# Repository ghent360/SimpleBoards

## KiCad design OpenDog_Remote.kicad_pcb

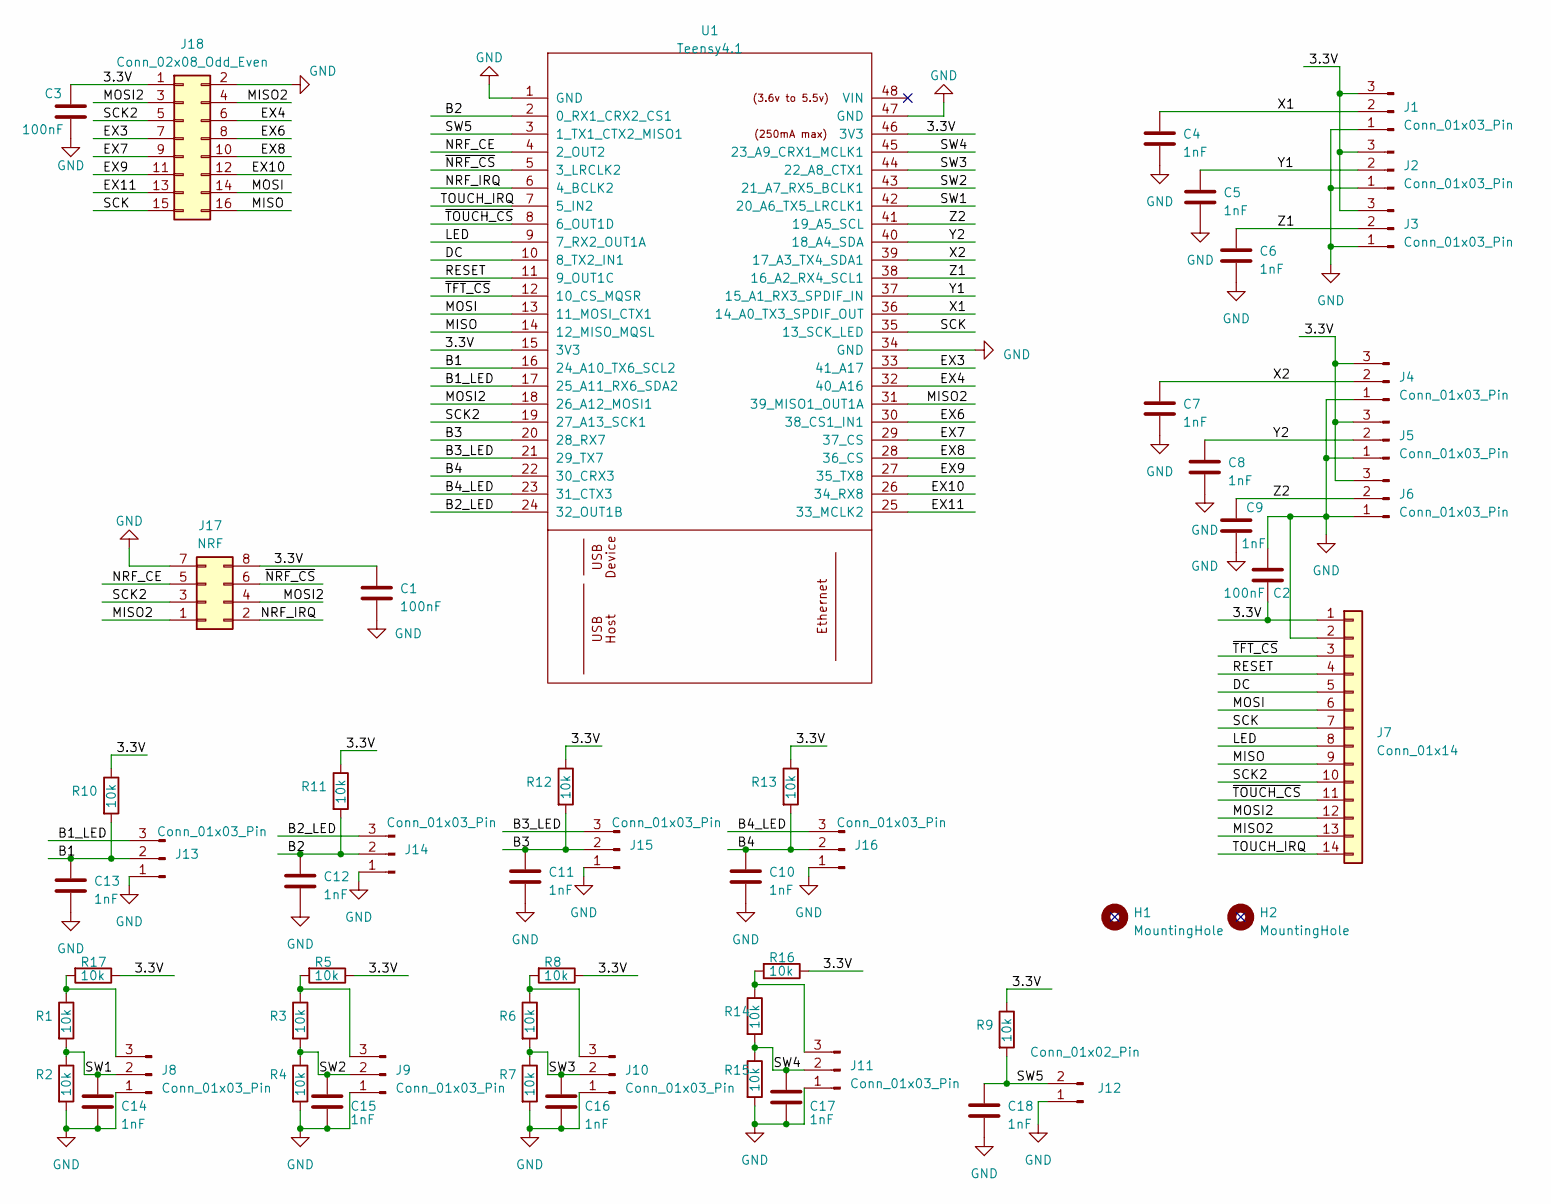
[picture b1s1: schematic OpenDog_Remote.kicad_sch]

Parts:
C1, C2, C3: 100nF; C_0603_1608Metric; JLC Part # C14663
C4, C5, C6, C7, C8, C9, C10, C11, C12, C13, C14, C15, C16, C17, C18: 1nF; C_0402_1005Metric; JLC Part # C1523
H1, H2: MountingHole; MountingHole_3.2mm_M3
J1, J2, J3, J4, J5, J6, J8, J9, J10, J11, J13, J14, J15, J16: Conn_01x03_Pin; JST_XH_B3B-XH-A_1x03_P2.50mm_Vertical; JLC Part # C722693
J7: Conn_01x14; PinHeader_1x14_P2.54mm_Vertical; JLC Part # C2905490
J12: Conn_01x02_Pin; JST_XH_B2B-XH-A_1x02_P2.50mm_Vertical; JLC Part # C2979476
J17: NRF; PinSocket_2x04_P2.54mm_Vertical; JLC Part # C2834799
J18: Conn_02x08_Odd_Even; PinSocket_2x08_P2.54mm_Vertical; JLC Part # C92267
R1, R2, R3, R4, R5, R6, R7, R8, R9, R10, R11, R12, R13, R14, R15, R16, R17: 10k; R_0402_1005Metric; JLC Part # C25744
U1: Teensy4.1; Teensy41-Simple

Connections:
/3.3V: C1.1, C2.2, C3.1, J1.3, J2.3, J3.3, J4.3, J5.3, J6.3, J7.1, J17.8, J18.1, R5.1, R8.1, R9.1, R10.1, R11.1, R12.1, R13.1, R16.1, R17.1, U1.15 (3V3), U1.46 (3V3)
/B1: C13.1, J13.2, R10.2, U1.16 (24_A10_TX6_SCL2)
/B1_LED: J13.3, U1.17 (25_A11_RX6_SDA2)
/B2: C12.1, J14.2, R11.2, U1.2 (0_RX1_CRX2_CS1)
/B2_LED: J14.3, U1.24 (32_OUT1B)
/B3: C11.1, J15.2, R12.2, U1.20 (28_RX7)
/B3_LED: J15.3, U1.21 (29_TX7)
/B4: C10.1, J16.2, R13.2, U1.22 (30_CRX3)
/B4_LED: J16.3, U1.23 (31_CTX3)
/DC: J7.5, U1.10 (8_TX2_IN1)
/EX3: J18.7, U1.33 (41_A17)
/EX4: J18.6, U1.32 (40_A16)
/EX6: J18.8, U1.30 (38_CS1_IN1)
/EX7: J18.9, U1.29 (37_CS)
/EX8: J18.10, U1.28 (36_CS)
/EX9: J18.11, U1.27 (35_TX8)
/EX10: J18.12, U1.26 (34_RX8)
/EX11: J18.13, U1.25 (33_MCLK2)
/LED: J7.8, U1.9 (7_RX2_OUT1A)
/MISO: J7.9, J18.16, U1.14 (12_MISO_MQSL)
/MISO2: J7.13, J17.1, J18.4, U1.31 (39_MISO1_OUT1A)
/MOSI: J7.6, J18.14, U1.13 (11_MOSI_CTX1)
/MOSI2: J7.12, J17.4, J18.3, U1.18 (26_A12_MOSI1)
/NRF_CE: J17.5, U1.4 (2_OUT2)
/NRF_IRQ: J17.2, U1.6 (4_BCLK2)
/RESET: J7.4, U1.11 (9_OUT1C)
/SCK: J7.7, J18.15, U1.35 (13_SCK_LED)
/SCK2: J7.10, J17.3, J18.5, U1.19 (27_A13_SCK1)
/SW1: C14.1, J8.2, R1.2, R2.1, U1.42 (20_A6_TX5_LRCLK1)
/SW2: C15.1, J9.2, R3.2, R4.1, U1.43 (21_A7_RX5_BCLK1)
/SW3: C16.1, J10.2, R6.2, R7.1, U1.44 (22_A8_CTX1)
/SW4: C17.1, J11.2, R14.2, R15.1, U1.45 (23_A9_CRX1_MCLK1)
/SW5: C18.1, J12.2, R9.2, U1.3 (1_TX1_CTX2_MISO1)
/TOUCH_IRQ: J7.14, U1.7 (5_IN2)
/X1: C4.1, J1.2, U1.36 (14_A0_TX3_SPDIF_OUT)
/X2: C7.1, J4.2, U1.39 (17_A3_TX4_SDA1)
/Y1: C5.1, J2.2, U1.37 (15_A1_RX3_SPDIF_IN)
/Y2: C8.1, J5.2, U1.40 (18_A4_SDA)
/Z1: C6.1, J3.2, U1.38 (16_A2_RX4_SCL1)
/Z2: C9.1, J6.2, U1.41 (19_A5_SCL)
/~NRF_CS: J17.6, U1.5 (3_LRCLK2)
/~TFT_CS: J7.3, U1.12 (10_CS_MQSR)
/~TOUCH_CS: J7.11, U1.8 (6_OUT1D)
GND: C1.2, C2.1, C3.2, C4.2, C5.2, C6.2, C7.2, C8.2, C9.2, C10.2, C11.2, C12.2, C13.2, C14.2, C15.2, C16.2, C17.2, C18.2, J1.1, J2.1, J3.1, J4.1, J5.1, J6.1, J7.2, J8.1, J9.1, J10.1, J11.1, J12.1, J13.1, J14.1, J15.1, J16.1, J17.7, J18.2, R2.2, R4.2, R7.2, R15.2, U1.1 (GND), U1.34 (GND), U1.47 (GND)
unnamed: J8.3, R1.1, R17.2
unnamed: J9.3, R3.1, R5.2
unnamed: J10.3, R6.1, R8.2
unnamed: J11.3, R14.1, R16.2

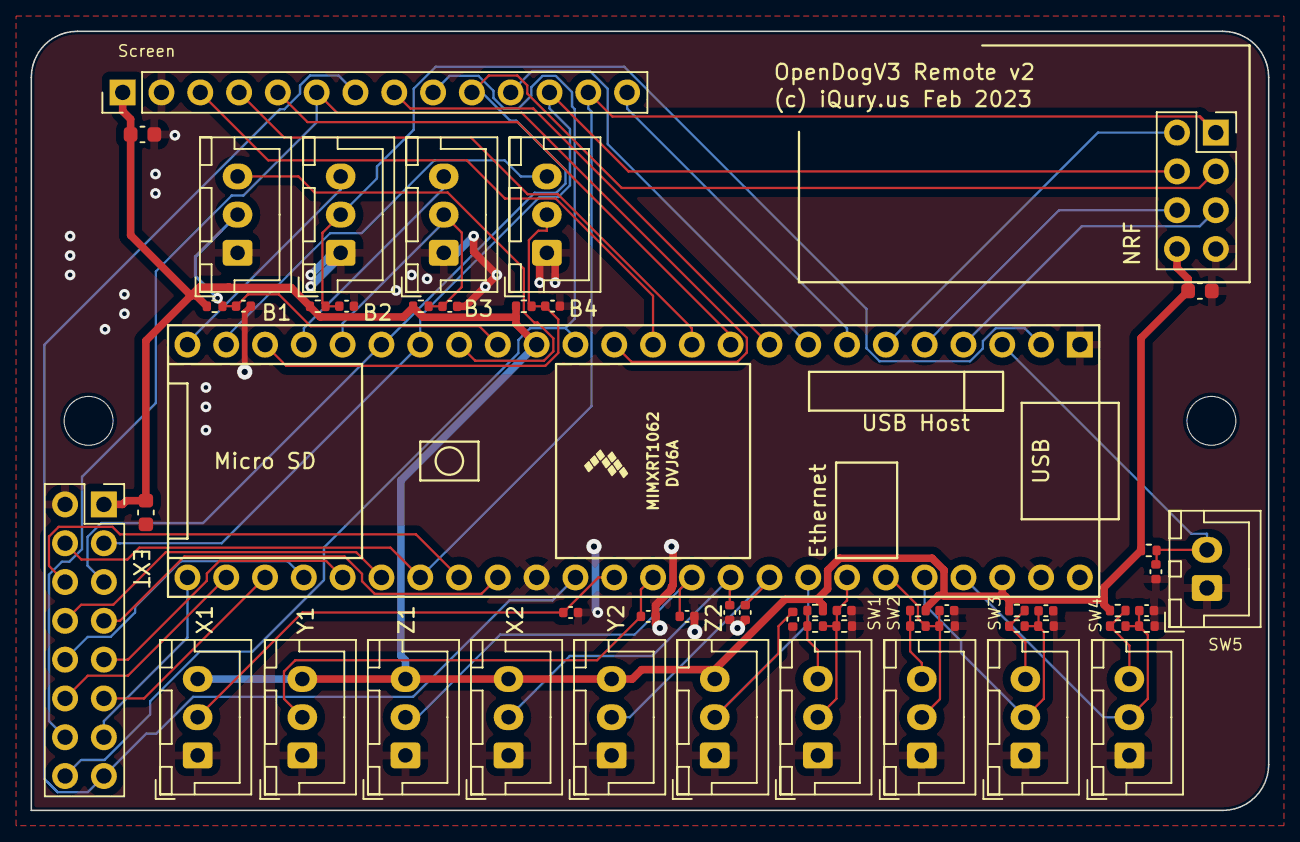
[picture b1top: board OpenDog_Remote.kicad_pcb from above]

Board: 2 copper layers, 81.0 x 51.0 mm, 56 parts (0 on the bottom side), 48 nets.

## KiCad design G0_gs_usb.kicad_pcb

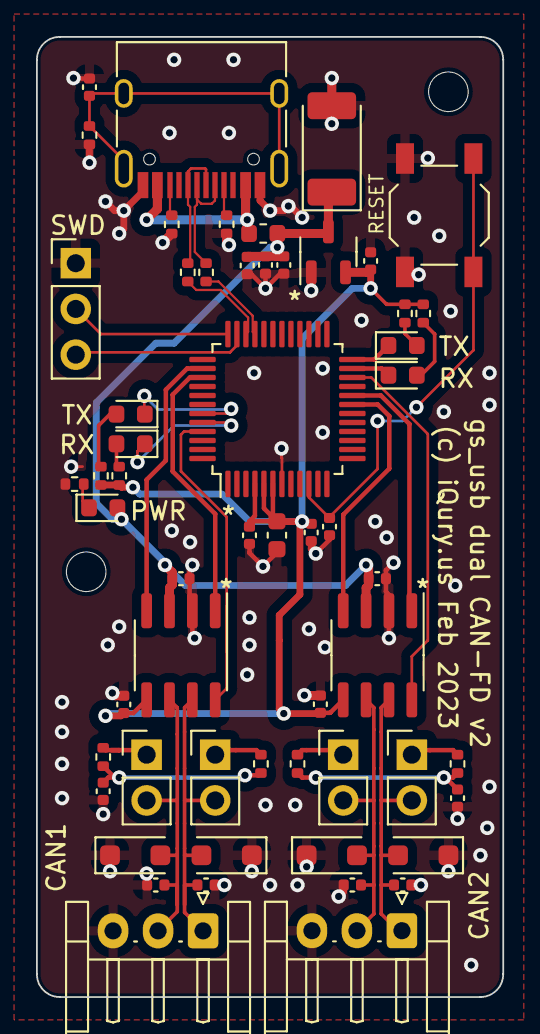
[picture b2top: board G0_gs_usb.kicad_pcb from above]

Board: 2 copper layers, 25.9 x 53.3 mm, 59 parts (0 on the bottom side), 39 nets.

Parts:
C1, C5, C6, C12, C15, C18, C19: 100nF; C_0402_1005Metric
C2, C7: 4700pF; C_0402_1005Metric
C3, C4, C8, C9: 47pF; C_0402_1005Metric
C10, C11, C13: 10nF; C_0402_1005Metric
C14: 10uF; C_0603_1608Metric
C16, C17: 1uF; C_0402_1005Metric
D1: 5.3V; D_MELF
D4, D5: TX; LED_0603_1608Metric
D6, D7, D8: RX; LED_0603_1608Metric
D9, D10, D11, D12: D_TVS; D_SOD-123F
F1: 500mA; Fuse_0603_1608Metric
H1, H2: MountingHole; MountingHole_2.2mm_M2
J1: USB_C_Receptacle_USB2.0; USB_C_Receptacle_HRO_TYPE-C-31-M-12
J2: CAN1; JST_EH_S3B-EH_1x03_P2.50mm_Horizontal
J3: CAN2; JST_EH_S3B-EH_1x03_P2.50mm_Horizontal
J4: Conn_01x03_Pin; PinHeader_1x03_P2.54mm_Vertical
JP1, JP2, JP3, JP4: Trm; PinHeader_1x02_P2.54mm_Vertical
R1: 100k; R_0402_1005Metric
R2, R3, R14: 5.1k; R_0402_1005Metric
R4, R5: 22; R_0402_1005Metric
R6, R7, R8, R9: 60.4; R_0402_1005Metric
R10, R11, R12, R13: 1k; R_0402_1005Metric
SW1: SW_Push_Dual; SW_SPST_TL3342
U1: STM32G0B1CBTx; LQFP-48_7x7mm_P0.5mm
U2, U3: TJA1042T-3; SOIC-8_3.9x4.9mm_P1.27mm
U4: XC6206PxxxMR; SOT-23-3

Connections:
/3.3V: C10.2, C11.2, C14.2, C15.2, C17.1, C18.2, R10.1, R11.1, R12.1, R13.1, U1.4 (VBAT), U1.5 (VREF+), U1.6 (VDD), U2.5 (VIO), U3.5 (VIO), U4.2 (VO)
/5V: C5.1, C6.1, C12.2, C13.2, C16.1, D1.1 (K), D8.2 (A), F1.1, U2.3 (VCC), U3.3 (VCC), U4.3 (VI)
/CAN1_N: C4.2, D12.2 (A2), J2.2, JP4.2 (B), U2.6 (CANL)
/CAN1_P: C3.1, D11.2 (A2), J2.1, JP3.2 (B), U2.7 (CANH)
/CAN1_RX: U1.38 (PD0), U2.4 (RXD)
/CAN1_RX_LED: D6.1 (K), U1.24 (PB12)
/CAN1_SBY: U1.45 (PB6), U2.8 (STB)
/CAN1_TX: U1.39 (PD1), U2.1 (TXD)
/CAN1_TX_LED: D4.1 (K), U1.23 (PB11)
/CAN2_N: C9.2, D10.2 (A2), J3.2, JP2.2 (B), U3.6 (CANL)
/CAN2_P: C8.1, D9.2 (A2), J3.1, JP1.2 (B), U3.7 (CANH)
/CAN2_RX: U1.19 (PB0), U3.4 (RXD)
/CAN2_RX_LED: D7.1 (K), U1.44 (PB5)
/CAN2_SBY: U1.22 (PB10), U3.8 (STB)
/CAN2_TX: U1.20 (PB1), U3.1 (TXD)
/CAN2_TX_LED: D5.1 (K), U1.43 (PB4)
/D+: J1.A6 (D+), J1.B6 (D+), R4.1
/D-: J1.A7 (D-), J1.B7 (D-), R5.1
/SDWIO: J4.3, U1.35 (PA13)
/SWCLK: J4.2, U1.36 (PA14)
/USB_DN: R5.2, U1.33 (PA11/PA9)
/USB_DP: R4.2, U1.34 (PA12/PA10)
/~RESET: C19.1, SW1.2, U1.10 (PF2)
GND: C1.2, C2.2, C3.2, C4.1, C5.2, C6.2, C7.2, C8.2, C9.1, C10.1, C11.1, C12.1, C13.1, C14.1, C15.1, C16.2, C17.2, C18.1, C19.2, D1.2 (A), D9.1 (A1), D10.1 (A1), D11.1 (A1), D12.1 (A1), J1.A1 (GND), J1.A12 (GND), J1.B1 (GND), J1.B12 (GND), J2.3, J3.3, J4.1, R1.2, R2.1, R3.1, R14.1, SW1.1, U1.7 (VSS), U2.2 (GND), U3.2 (GND), U4.1 (GND)
unnamed: C2.1, R8.2, R9.2
unnamed: C7.1, R6.2, R7.2
unnamed: D4.2 (A), R10.2
unnamed: D5.2 (A), R11.2
unnamed: D6.2 (A), R12.2
unnamed: D7.2 (A), R13.2
unnamed: D8.1 (K), R14.2
unnamed: F1.2, J1.A4 (VBUS), J1.A9 (VBUS), J1.B4 (VBUS), J1.B9 (VBUS)
unnamed: J1.A5 (CC1), R3.2
unnamed: J1.B5 (CC2), R2.2
unnamed: C1.1, J1.S1 (SHIELD), R1.1
unnamed: JP1.1 (A), R6.1
unnamed: JP2.1 (A), R7.1
unnamed: JP3.1 (A), R8.1
unnamed: JP4.1 (A), R9.1

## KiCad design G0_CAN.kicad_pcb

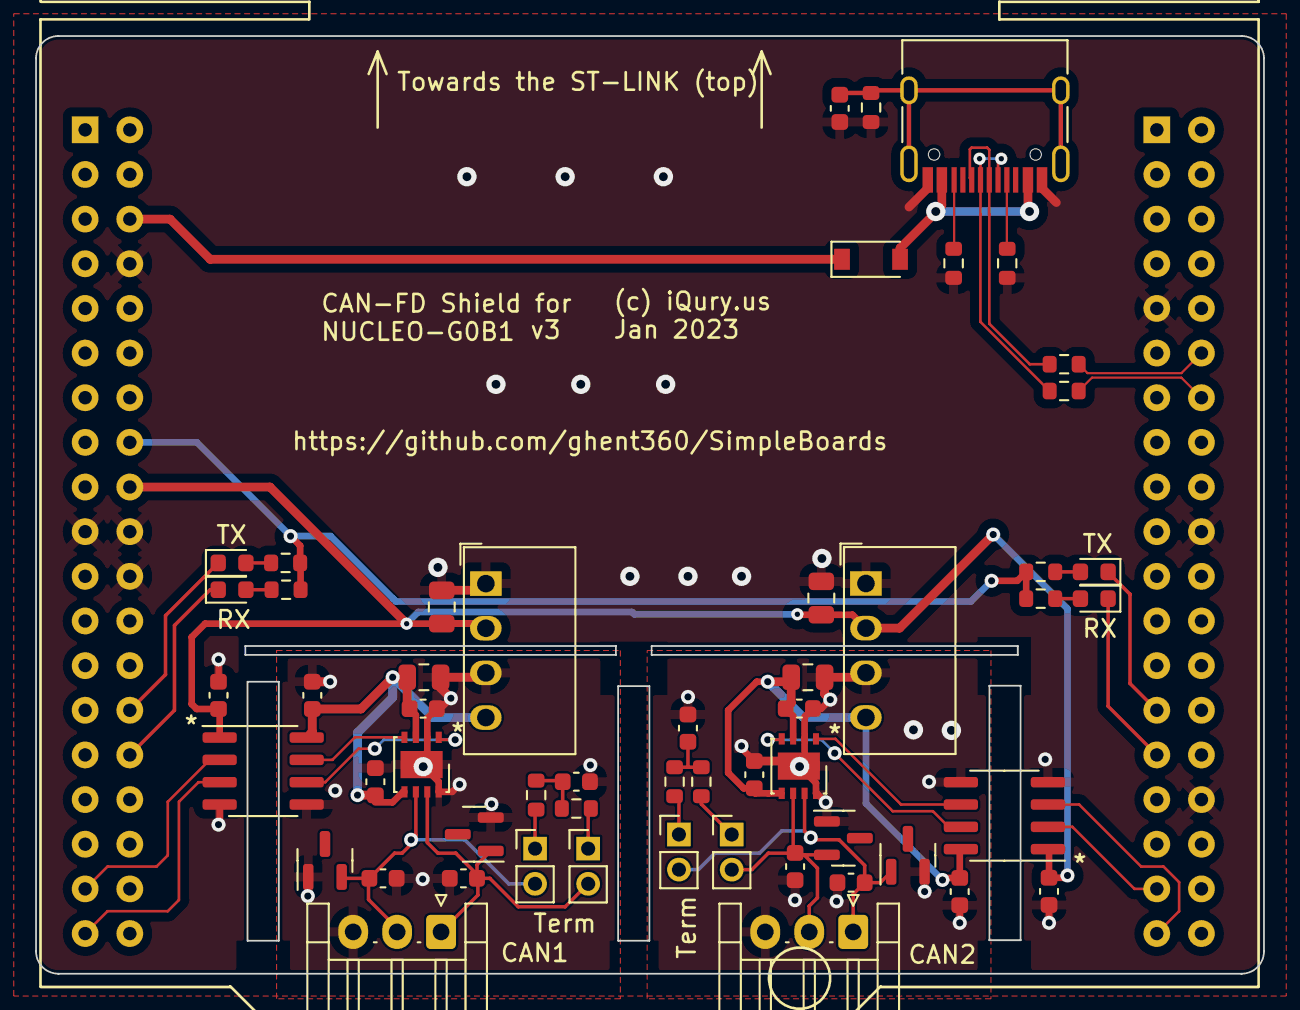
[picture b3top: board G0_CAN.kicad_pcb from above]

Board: 2 copper layers, 69.8 x 53.3 mm, 55 parts (0 on the bottom side), 42 nets.

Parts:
C1, C5, C6, C16, C17, C18, C19: 100nF; C_0603_1608Metric
C2, C7: 4700pF; C_0603_1608Metric
C3, C4, C8, C9: 47pF; C_0603_1608Metric
C10, C11: 10nF; C_0603_1608Metric
C12, C13, C14, C15: 4.7uF; C_0805_2012Metric
D1: B5819W; D_SOD-123
D2, D3, D4, D5: MMBZ27VC; SOT-23
D6, D7: TX; LED_0603_1608Metric
D8, D9: RX; LED_0603_1608Metric
J1: USB_C_Receptacle_USB2.0; USB_C_Receptacle_HRO_TYPE-C-31-M-12
J2: CAN1; JST_EH_S3B-EH_1x03_P2.50mm_Horizontal
J3: CAN2; JST_EH_S3B-EH_1x03_P2.50mm_Horizontal
JP1, JP2, JP3, JP4: Trm; PinHeader_1x02_P2.00mm_Vertical
R1: 100k; R_0603_1608Metric
R2, R3: 5.1k; R_0603_1608Metric
R4, R5, R10, R11, R12, R13: 22; R_0603_1608Metric
R6, R7, R8, R9: 60.4; R_0603_1608Metric
U1: Nucleo-64-G0B1; Nucleo-64
U2, U3: TJA1051TK-3; DFN-8-1EP_3x3mm_P0.65mm_EP1.55x2.4mm
U4, U5: CRE1S0505S3C; Converter_DCDC_Murata_CRE1xxxxxx3C_THT
U6, U7: NSi8121N0; SOIC-8_3.9x4.9mm_P1.27mm

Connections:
/3.3V: R10.1, R11.1, R12.1, R13.1, U1.16 (3.3v)
/5V: C13.1, C15.1, C16.1, C18.1, U1.18 (5V), U4.2 (+VIN), U5.2 (+VIN), U6.1 (VDD1), U7.1 (VDD1)
/5V-CAN1: C6.1, C11.2, C14.1, C17.1, U3.3 (VCC), U3.5 (VIO), U5.4 (+VOUT), U6.8 (VDD2)
/5V-CAN2: C5.1, C10.2, C12.1, C19.1, U2.3 (VCC), U2.5 (VIO), U4.4 (+VOUT), U7.8 (VDD2)
/CAN1_H: C3.1, D4.1 (K), J2.1, JP3.2 (B), U3.7 (CANH)
/CAN1_L: C4.2, D5.2 (K), J2.2, JP4.2 (B), U3.6 (CANL)
/CAN1_RX: U1.35 (PC2), U6.2 (VOA)
/CAN1_RX_ISO: U3.4 (RXD), U6.7 (VIA)
/CAN1_RX_LED: D8.1 (K), U1.30 (PA1)
/CAN1_TX: U1.37 (PC3), U6.3 (VIB)
/CAN1_TX_ISO: U3.1 (TXD), U6.6 (VOB)
/CAN1_TX_LED: D6.1 (K), U1.28 (PA0)
/CAN2_H: C8.1, D2.1 (K), J3.1, JP1.2 (B), U2.7 (CANH)
/CAN2_L: C9.2, D3.2 (K), J3.2, JP2.2 (B), U2.6 (CANL)
/CAN2_RX: U1.73 (PC4), U7.2 (VOA)
/CAN2_RX_ISO: U2.4 (RXD), U7.7 (VIA)
/CAN2_RX_LED: D9.1 (K), U1.67 (PB5)
/CAN2_TX: U1.75 (PC5), U7.3 (VIB)
/CAN2_TX_ISO: U2.1 (TXD), U7.6 (VOB)
/CAN2_TX_LED: D7.1 (K), U1.65 (PB4)
/D+: J1.A6 (D+), J1.B6 (D+), R4.1
/D-: J1.A7 (D-), J1.B7 (D-), R5.1
/E5V: D1.1 (K), U1.6 (E5V)
/USB_DN: R5.2, U1.52 (PA11)
/USB_DP: R4.2, U1.50 (PA12)
GND: C1.2, C13.2, C15.2, C16.2, C18.2, J1.A1 (GND), J1.A12 (GND), J1.B1 (GND), J1.B12 (GND), R1.2, R2.1, R3.1, U1.8 (GND), U1.19 (GND), U1.20 (GND), U1.22 (GND), U1.47 (GND), U1.58 (GND), U1.70 (AGND), U4.1 (-VIN), U5.1 (-VIN), U6.4 (GND1), U7.4 (GND1)
GND1: C2.2, C3.2, C4.1, C6.2, C11.1, C14.2, C17.2, D4.2 (K), D5.1 (K), J2.3, U3.2 (GND), U3.8 (S), U3.9 (GND), U5.3 (-VOUT), U6.5 (GND2)
GND2: C5.2, C7.2, C8.2, C9.1, C10.1, C12.2, C19.2, D2.2 (K), D3.1 (K), J3.3, U2.2 (GND), U2.8 (S), U2.9 (GND), U4.3 (-VOUT), U7.5 (GND2)
unnamed: C2.1, R8.2, R9.2
unnamed: C7.1, R6.2, R7.2
unnamed: D1.2 (A), J1.A4 (VBUS), J1.A9 (VBUS), J1.B4 (VBUS), J1.B9 (VBUS)
unnamed: D6.2 (A), R10.2
unnamed: D7.2 (A), R11.2
unnamed: D8.2 (A), R12.2
unnamed: D9.2 (A), R13.2
unnamed: J1.A5 (CC1), R3.2
unnamed: J1.B5 (CC2), R2.2
unnamed: C1.1, J1.S1 (SHIELD), R1.1
unnamed: JP1.1 (A), R6.1
unnamed: JP2.1 (A), R7.1
unnamed: JP3.1 (A), R8.1
unnamed: JP4.1 (A), R9.1

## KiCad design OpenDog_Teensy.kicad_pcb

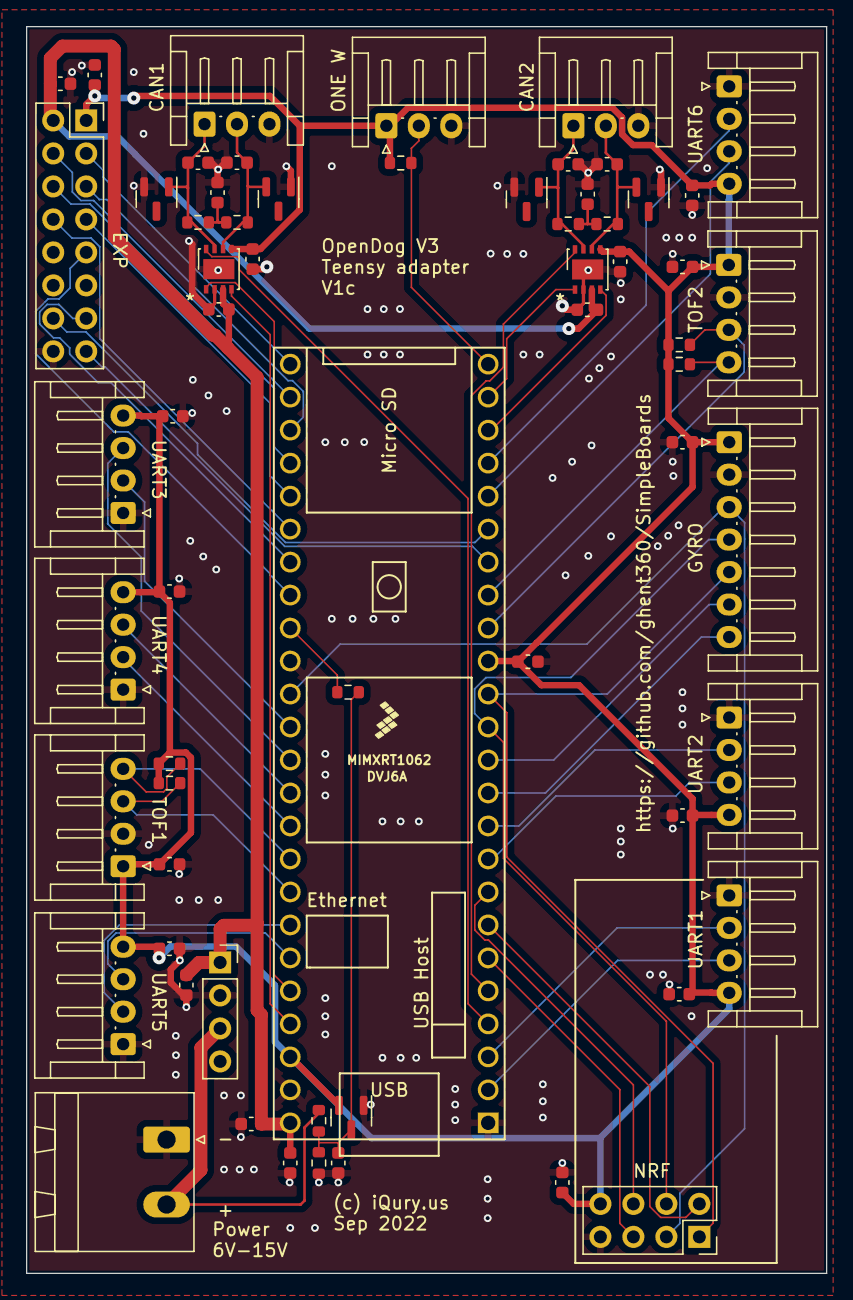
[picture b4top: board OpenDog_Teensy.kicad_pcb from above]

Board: 2 copper layers, 61.6 x 96.0 mm, 63 parts (0 on the bottom side), 53 nets.

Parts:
C1, C2, C3, C4, C5, C6, C15, C16, C17, C18, C19, C20, C21, C22, C23, C24, C25, C26, C27: 100nF; C_0603_1608Metric
C7, C10: 4700pF; C_0603_1608Metric
C8, C9, C11, C12: 47pF; C_0603_1608Metric
C13, C14: 10nF; C_0603_1608Metric
D1, D2, D3, D4: MMBZ27VC; SOT-23
D5: BAT54S; SOT-23
J1: NRF; PinSocket_2x04_P2.54mm_Vertical
J2: TOF1; JST_EH_S4B-EH_1x04_P2.50mm_Horizontal
J3: TOF2; JST_EH_S4B-EH_1x04_P2.50mm_Horizontal
J4: IMU; JST_EH_S7B-EH_1x07_P2.50mm_Horizontal
J5: One W; JST_EH_S3B-EH_1x03_P2.50mm_Horizontal
J6: UART1; JST_EH_S4B-EH_1x04_P2.50mm_Horizontal
J7: UART2; JST_EH_S4B-EH_1x04_P2.50mm_Horizontal
J8: UART3; JST_EH_S4B-EH_1x04_P2.50mm_Horizontal
J9: UART4; JST_EH_S4B-EH_1x04_P2.50mm_Horizontal
J10: UART5; JST_EH_S4B-EH_1x04_P2.50mm_Horizontal
J11: UART6; JST_EH_S4B-EH_1x04_P2.50mm_Horizontal
J12: CAN1; JST_EH_S3B-EH_1x03_P2.50mm_Horizontal
J13: CAN2; JST_EH_S3B-EH_1x03_P2.50mm_Horizontal
J14: EXP; PinSocket_2x08_P2.54mm_Vertical
J15: Power; PhoenixContact_MSTBA_2,5_2-G_1x02_P5.00mm_Horizontal
J16: VReg; PinSocket_1x04_P2.54mm_Vertical
R1, R2, R3, R4: 60.4; R_0603_1608Metric
R5, R9, R10, R11, R12: 1k; R_0603_1608Metric
R6: 82k; R_0603_1608Metric
R7: 22k; R_0603_1608Metric
R8: 10k; R_0603_1608Metric
U1: Teensy4.1; Teensy41-Simple
U2, U3: TJA1042TK-3; DFN-8-1EP_3x3mm_P0.65mm_EP1.55x2.4mm

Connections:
/3.3V: C13.1, C14.1, C15.1, C17.1, C18.1, C19.1, C20.1, C21.1, C22.1, C23.1, C24.1, C25.1, C26.1, C27.1, D5.2, J1.8, J2.1, J3.1, J4.1, J5.1, J6.4, J7.4, J8.4, J9.4, J10.4, J11.4, J14.1, R5.1, R9.1, R10.1, R11.1, R12.1, U1.15 (3V3), U1.46 (3V3), U2.5 (VIO), U3.5 (VIO)
/5V: C1.1, C2.1, C3.1, C4.1, C5.1, C6.1, J14.2, J16.1, U1.48 (VIN), U2.3 (VCC), U3.3 (VCC)
/CAN1_H: C8.1, D1.1 (K), J12.1, R1.1, U2.7 (CANH)
/CAN1_L: C9.2, D2.2 (K), J12.2, R2.2, U2.6 (CANL)
/CAN1_RX: U1.45 (23_A9_CRX1_MCLK1), U2.4 (RXD)
/CAN1_SB: U1.4 (2_OUT2), U2.8 (STB)
/CAN1_TX: U1.44 (22_A8_CTX1), U2.1 (TXD)
/CAN2_H: C11.1, D3.1 (K), J13.1, R3.1, U3.7 (CANH)
/CAN2_L: C12.2, D4.2 (K), J13.2, R4.2, U3.6 (CANL)
/CAN2_RX: U1.22 (30_CRX3), U3.4 (RXD)
/CAN2_SB: U1.5 (3_LRCLK2), U3.8 (STB)
/CAN2_TX: U1.23 (31_CTX3), U3.1 (TXD)
/EXT1: J14.3, U1.25 (33_MCLK2)
/EXT2: J14.4, U1.26 (34_RX8)
/EXT3: J14.5, U1.27 (35_TX8)
/EXT4: J14.6, U1.28 (36_CS)
/EXT5: J14.7, U1.29 (37_CS)
/EXT6: J14.8, U1.30 (38_CS1_IN1)
/EXT7: J14.9, U1.32 (40_A16)
/MISO: J1.1, J4.5, U1.14 (12_MISO_MQSL)
/MISO1: J14.13, U1.31 (39_MISO1_OUT1A)
/MOSI: J1.4, J4.4, U1.13 (11_MOSI_CTX1)
/MOSI1: J14.15, U1.18 (26_A12_MOSI1)
/NRF_ENA: J1.5, U1.6 (4_BCLK2)
/NRF_IRQ: J1.2, U1.7 (5_IN2)
/ONE_W: J5.2, R5.2, U1.24 (32_OUT1B)
/RX1: J6.3, U1.2 (0_RX1_CRX2_CS1)
/RX2: J7.3, U1.9 (7_RX2_OUT1A)
/RX3: J8.3, U1.37 (15_A1_RX3_SPDIF_IN)
/RX4: J9.3, U1.38 (16_A2_RX4_SCL1)
/RX5: J10.3, U1.43 (21_A7_RX5_BCLK1)
/RX6: J11.3, U1.20 (28_RX7)
/SCK: J1.3, J4.3, U1.35 (13_SCK_LED)
/SCK1: J14.14, U1.19 (27_A13_SCK1)
/SCL1: J2.3, R9.2, U1.41 (19_A5_SCL)
/SCL2: J3.3, R12.2, U1.16 (24_A10_TX6_SCL2)
/SDA1: J2.4, R10.2, U1.40 (18_A4_SDA)
/SDA2: J3.4, R11.2, U1.17 (25_A11_RX6_SDA2)
/TX1: J6.2, U1.3 (1_TX1_CTX2_MISO1)
/TX2: J7.2, U1.10 (8_TX2_IN1)
/TX3: J8.2, U1.36 (14_A0_TX3_SPDIF_OUT)
/TX4: J9.2, U1.39 (17_A3_TX4_SDA1)
/TX5: J10.2, U1.42 (20_A6_TX5_LRCLK1)
/TX6: J11.2, U1.21 (29_TX7)
/V_MON: R8.1, U1.33 (41_A17)
/Vbat: J15.2, J16.3, R6.1
/~CS_BMP: J4.7, U1.11 (9_OUT1C)
/~CS_IMU: J4.6, U1.12 (10_CS_MQSR)
/~CS_NRF: J1.6, U1.8 (6_OUT1D)
GND: C1.2, C2.2, C3.2, C4.2, C5.2, C6.2, C7.2, C8.2, C9.1, C10.2, C11.2, C12.1, C13.2, C14.2, C15.2, C16.2, C17.2, C18.2, C19.2, C20.2, C21.2, C22.2, C23.2, C24.2, C25.2, C26.2, C27.2, D1.2 (K), D2.1 (K), D3.2 (K), D4.1 (K), D5.1, J1.7, J2.2, J3.2, J4.2, J5.3, J6.1, J7.1, J8.1, J9.1, J10.1, J11.1, J12.3, J13.3, J14.16, J15.1, J16.2, R7.2, U1.1 (GND), U1.34 (GND), U1.47 (GND), U2.2 (GND), U2.9 (GND), U3.2 (GND), U3.9 (GND)
unnamed: C7.1, R1.2, R2.1
unnamed: C10.1, R3.2, R4.1
unnamed: C16.1, D5.3, R6.2, R7.1, R8.2

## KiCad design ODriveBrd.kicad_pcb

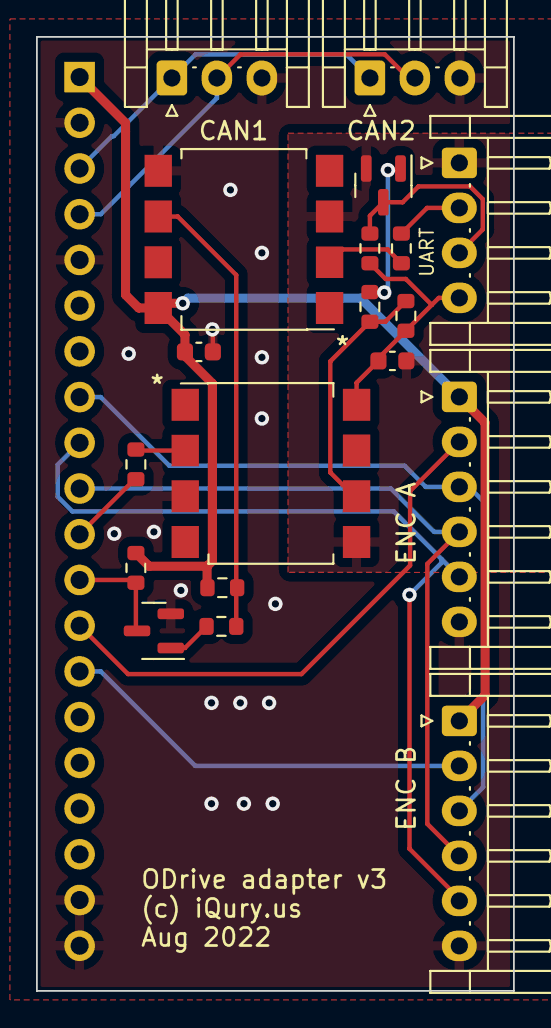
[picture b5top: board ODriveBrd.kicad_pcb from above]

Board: 2 copper layers, 26.5 x 53.0 mm, 20 parts (1 on the bottom side), 21 nets.

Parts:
C1, C2: 100nF; C_0603_1608Metric
J1: ODrive; PinHeader_1x20_P2.54mm_Vertical
J2: CAN1; JST_EH_S3B-EH_1x03_P2.50mm_Horizontal
J3: CAN2; JST_EH_S3B-EH_1x03_P2.50mm_Horizontal
J4: ENC A; JST_EH_S6B-EH_1x06_P2.50mm_Horizontal
J5: ENC B; JST_EH_S6B-EH_1x06_P2.50mm_Horizontal
J6: UART; JST_EH_S4B-EH_1x04_P2.50mm_Horizontal
Q1, Q2: 2N7002; SOT-23
R1, R4, R6, R7: 200; R_0603_1608Metric
R2, R3, R5, R8: 1k; R_0603_1608Metric
U1, U2: 6N137; SSO-8_6.7x9.8mm_P2.54mm_Clearance8mm

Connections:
/3.3V: C1.1, J1.1, J4.1, J5.1, R3.1, R8.1, U2.8 (VCC)
/3.3V-in: C2.1, J6.4, R2.1, R5.1, U1.8 (VCC)
/GND-in: C2.2, J6.1, Q1.2 (S), U1.5 (GND), U2.3 (C)
/RX: J1.12, Q2.3 (D), R8.2
/RX-in: J6.2, R1.2
/TX: J1.11, R4.1
/TX-in: J6.3, Q1.3 (D), R5.2
GND: C1.2, J1.2, J1.5, J1.19, J1.20, J2.3, J3.3, J4.6, J5.6, Q2.2 (S), U1.3 (C), U2.5 (GND)
unnamed: J1.3, J2.1, J3.1
unnamed: J1.4, J2.2, J3.2
unnamed: J1.8, J4.3, J5.3
unnamed: J1.9, J4.5, J5.5
unnamed: J1.10, J4.4, J5.4
unnamed: J1.13, J4.2
unnamed: J1.14, J5.2
unnamed: Q1.1 (G), R6.1
unnamed: Q2.1 (G), R7.1
unnamed: R4.2, U1.2 (A)
unnamed: R2.2, R6.2, U1.6 (VO)
unnamed: R1.1, U2.2 (A)
unnamed: R3.2, R7.2, U2.6 (VO)

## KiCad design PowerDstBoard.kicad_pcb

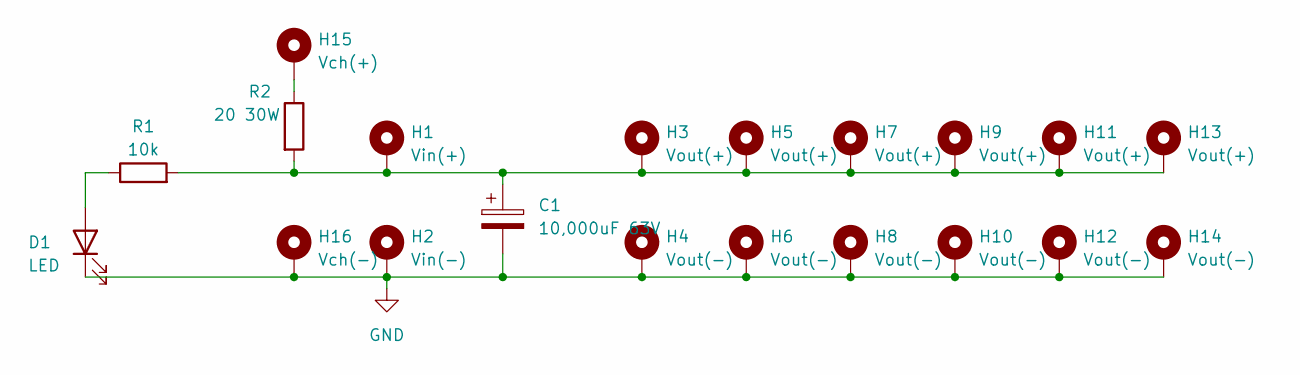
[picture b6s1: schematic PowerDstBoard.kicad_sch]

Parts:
C1: 10,000uF 63V; CP_Radial_D35.0mm_P10.00mm_SnapIn
D1: LED; LED_0603_1608Metric
H1: Vin(+); MountingHole_5.3mm_M5_DIN965_Pad
H2: Vin(-); MountingHole_5.3mm_M5_DIN965_Pad
H3, H5, H7, H9, H11, H13: Vout(+); MountingHole_3.2mm_M3_DIN965_Pad
H4, H6, H8, H10, H12, H14: Vout(-); MountingHole_3.2mm_M3_DIN965_Pad
H15: Vch(+); MountingHole_3.2mm_M3_DIN965_Pad
H16: Vch(-); MountingHole_3.2mm_M3_DIN965_Pad
R1: 10k; R_0603_1608Metric
R2: 20 30W; TO-220-2_Vertical

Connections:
GND: C1.2, D1.1 (K), H2.1, H4.1, H6.1, H8.1, H10.1, H12.1, H14.1, H16.1
unnamed: C1.1, H1.1, H3.1, H5.1, H7.1, H9.1, H11.1, H13.1, R1.2, R2.2
unnamed: D1.2 (A), R1.1
unnamed: H15.1, R2.1

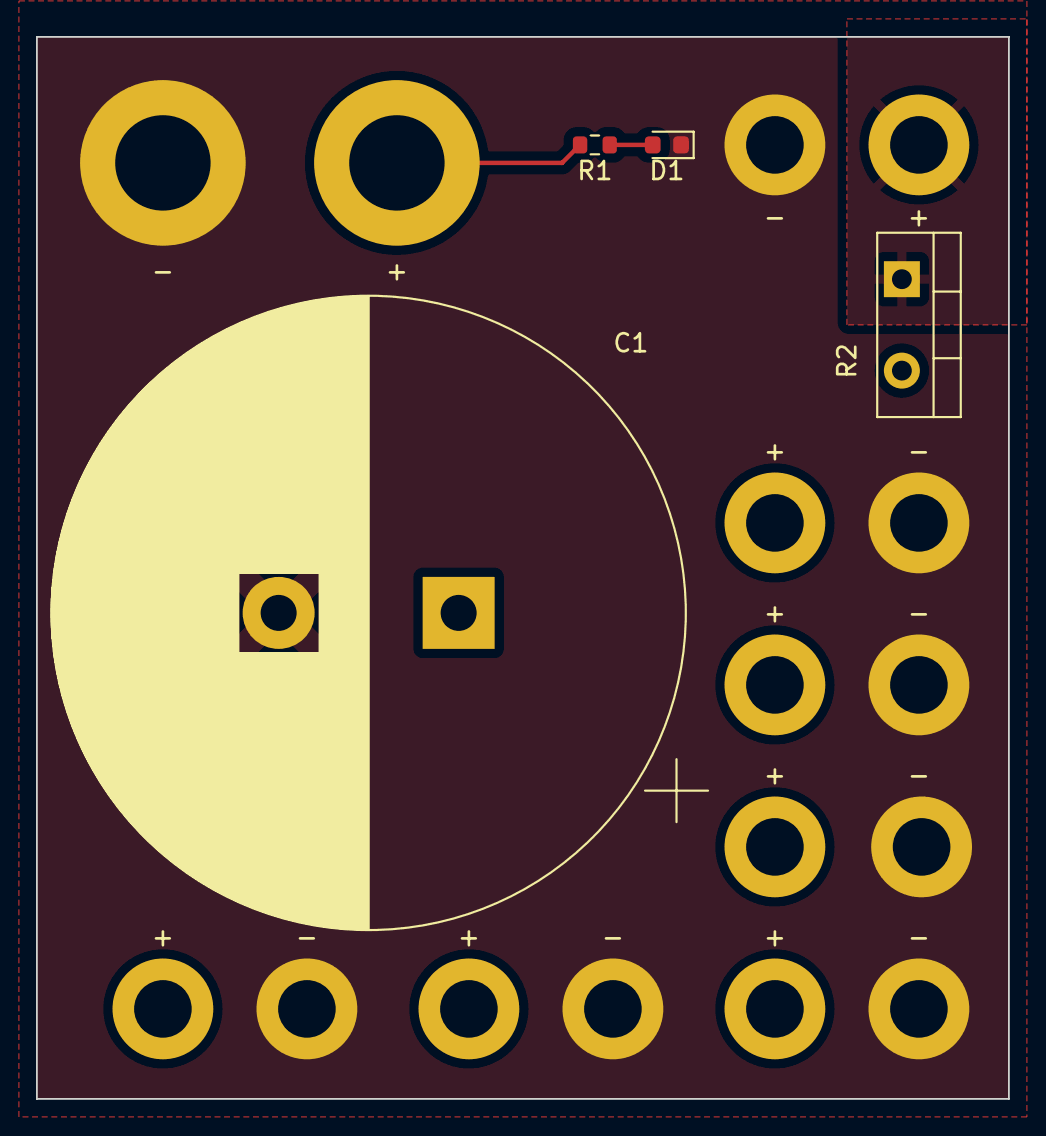
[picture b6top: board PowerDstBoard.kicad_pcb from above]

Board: 2 copper layers, 54.0 x 59.0 mm, 20 parts (0 on the bottom side), 4 nets.

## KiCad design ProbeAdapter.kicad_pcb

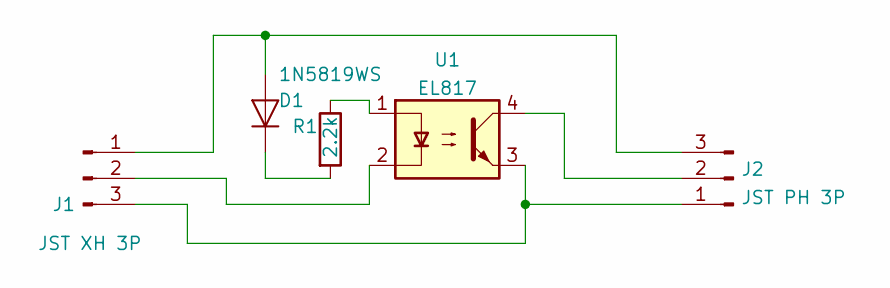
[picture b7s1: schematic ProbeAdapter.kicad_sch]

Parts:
D1: 1N5819WS; D_SOD-323; LCSC C191023
J1: JST XH 3P; JST_XH_B3B-XH-A_1x03_P2.50mm_Vertical
J2: JST PH 3P; JST_PH_B3B-PH-K_1x03_P2.00mm_Vertical
R1: 2.2k; R_0402_1005Metric; LCSC C25879
U1: EL817; SOP254P1030X390-4N; LCSC C106900

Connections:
unnamed: D1.2 (A), J1.1, J2.3
unnamed: D1.1 (K), R1.2
unnamed: J1.2, U1.2
unnamed: J1.3, J2.1, U1.3
unnamed: J2.2, U1.4
unnamed: R1.1, U1.1

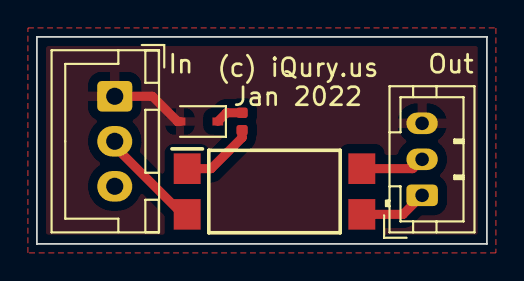
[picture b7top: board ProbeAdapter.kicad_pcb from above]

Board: 2 copper layers, 25.0 x 11.5 mm, 5 parts (0 on the bottom side), 6 nets.

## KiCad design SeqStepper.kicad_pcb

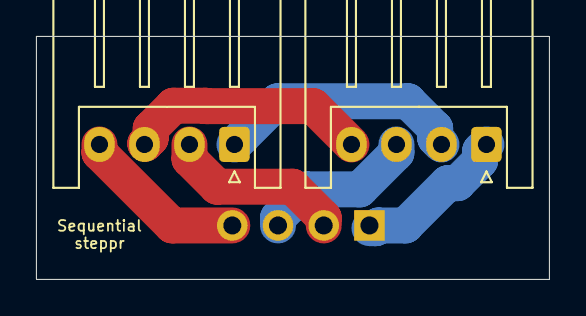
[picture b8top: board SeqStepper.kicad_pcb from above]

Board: 2 copper layers, 28.5 x 13.5 mm, 3 parts (1 on the bottom side), 6 nets.

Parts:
J1: In; PinSocket_1x04_P2.54mm_Horizontal
J2: ST1; JST_XH_S4B-XH-A_1x04_P2.50mm_Horizontal
J3: ST2; JST_XH_S4B-XH-A_1x04_P2.50mm_Horizontal

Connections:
unnamed: J1.1, J2.1
unnamed: J1.2, J3.2
unnamed: J1.3, J2.3
unnamed: J1.4, J3.4
unnamed: J2.2, J3.1
unnamed: J2.4, J3.3

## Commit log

2019-11-30 Initial commit.
2019-11-30 Completed SeqStepper.
2019-11-30 Add gerber files.
2019-12-01 Add 8 pin stepper adapter.
2021-01-05 Added two motor connector converter boards.
2021-01-05 Update traces with more copper.
2021-01-08 Update MotorJST with the correct 2mm pitch connector.
2022-02-12 Add new boards.
2022-02-12 Add Power distribution board.
2022-08-03 Updated ODrive adapter with isolated serial.
2022-08-03 Add chip start pin mark.
2022-08-04 Added OpenDog Teensy adapter: - 6x serial ports - 2 CAN ports - 2 TOF ports - 1 IMU port - 1 One Wire port - NRF wireless connector
    Unused pins are routed to EXP port.
2022-08-05 Added labels to the silkscreen
2022-08-05 Added input voltage monitoring cirquit.
2022-08-05 Improved routing.
2022-08-05 Added more filtering capacitors on the 3.3v rail one for each connector.
2022-08-14 Update OpenDog board part numbers. Small routing changes.
2022-08-14 Added I2C pullups to the OpenDog board.
2022-08-14 Fixed NRF connector pinout.
2022-08-25 Add inverters to the opto serial adapter.
2022-09-02 Add more vias. Resolve DRC warnings.
2022-09-02 OpenDog_Teensy - add buck converter socket. Move the battery monitor to the battery input instead of the 5V input in the old version.
2022-09-02 OpenDog_Teensy - Update routing. Sent to fab.
2022-12-23 Add new project STM32G0B1 CAN hat for the Nucleo-64-G0B1 dev kit.
2022-12-23 Routed the G0B1 CAN board.
2022-12-23 Fix S pin on the CAN transcievers to low, so they are active. Fix USB data pin routing.
2022-12-24 Update the CAN filter network routing.
2022-12-25 Make the G0-CAN board use isolated CAN.
2023-01-04 Flip the nucleo connector.
2023-01-23 Add TX/RX leds to the CAN shield.
2023-01-24 Add OpenDog Remote Board.
2023-01-24 Added JLCPCB part #, round some board corners.
2023-01-24 Output fab files.
2023-01-24 Update JPC part #s.
2023-01-25 Add terminator jumpers.
2023-01-31 Add dual CAN USB adapter.
2023-02-01 Update footprints on R and C to 0402. Added 5V protection. Routed CAN RX/TX as diff pairs.
2023-02-01 Use better TVS diodes.
2023-02-03 Update TVS diodes. Add reset button.
2023-02-07 Update the OpenDog remote board.
2023-02-07 Move the SW5 connector away fromt he USB cable.
2023-02-11 Add filtering caps on the switches and pots.
2023-02-20 Update net labels to match the purpose of the pins.
2023-02-20 Separate screen and NRF/Touch SPI channels.
